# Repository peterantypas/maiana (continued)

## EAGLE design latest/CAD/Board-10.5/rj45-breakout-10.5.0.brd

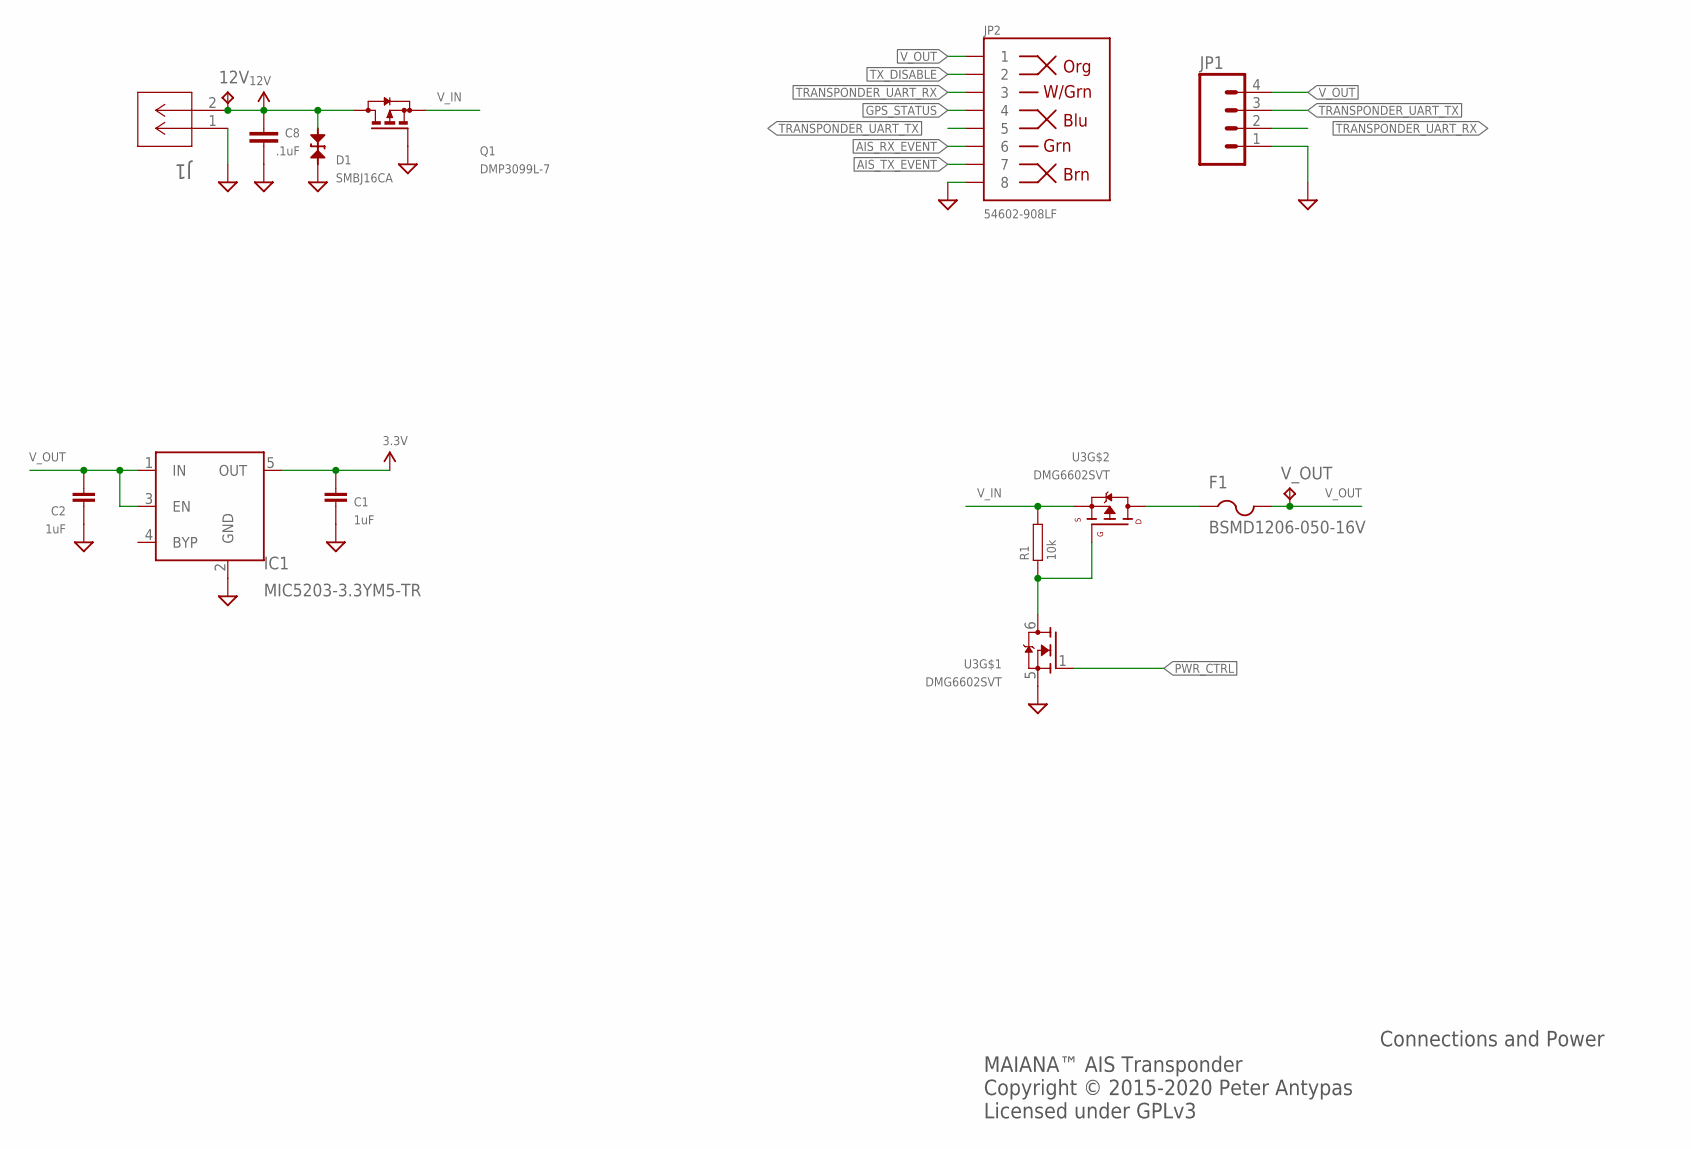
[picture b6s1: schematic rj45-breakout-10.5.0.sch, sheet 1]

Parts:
12V: TPTP20R; TP20R
C1, C2: 1uF; 0603
C8: .1uF; 0603-CAP; PARTNO GRM188R71E223KA01D
D1: SMBJ16CA; SMB-BIDIR
F1: BSMD1206-050-16V; R1206
IC1: MIC5203-3.3YM5-TR; SOT23-5
J1: OSTVN02A150; CONN_OSTVN02A150_OST
JP1: M04PTH; 1X04
JP2: 54602-908LF; RJ45-8
Q1: DMP3099L-7; SOT23
R1: 10k; 0603
U3: DMG6602SVT; SOT23-6
V_OUT: TPTP20R; TP20R

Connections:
3.3V: C1.P$1 (1), IC1.5 (OUT); also elsewhere on the board
12V: 12V.TP, C8.1, D1.A, J1.2, Q1.3 (D)
AIS_RX_EVENT: JP2.6; also elsewhere on the board
AIS_TX_EVENT: JP2.7; also elsewhere on the board
GND: C1.P$2 (2), C2.P$2 (2), C8.2, D1.C, IC1.2 (GND), J1.1, JP1.1, JP2.8, Q1.1 (G), U3.5 (S); also elsewhere on the board
GPS_STATUS: JP2.4; also elsewhere on the board
unnamed: R1.P$1, U3.3 (G), U3.6 (D)
unnamed: F1.1, U3.4 (D)
PWR_CTRL: U3.1 (G); also elsewhere on the board
TRANSPONDER_UART_RX: JP1.2, JP2.3
TRANSPONDER_UART_TX: JP1.3, JP2.5
TX_DISABLE: JP2.2; also elsewhere on the board
V_IN: Q1.2 (S), R1.P$2, U3.2 (S); also elsewhere on the board
V_OUT: C2.P$1 (1), F1.2, IC1.1 (IN), IC1.3 (EN), JP1.4, JP2.1, V_OUT.TP

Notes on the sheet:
MAIANA™ AIS Transponder Copyright © 2015-2020 Peter Antypas Licensed under GPLv3
Connections and Power

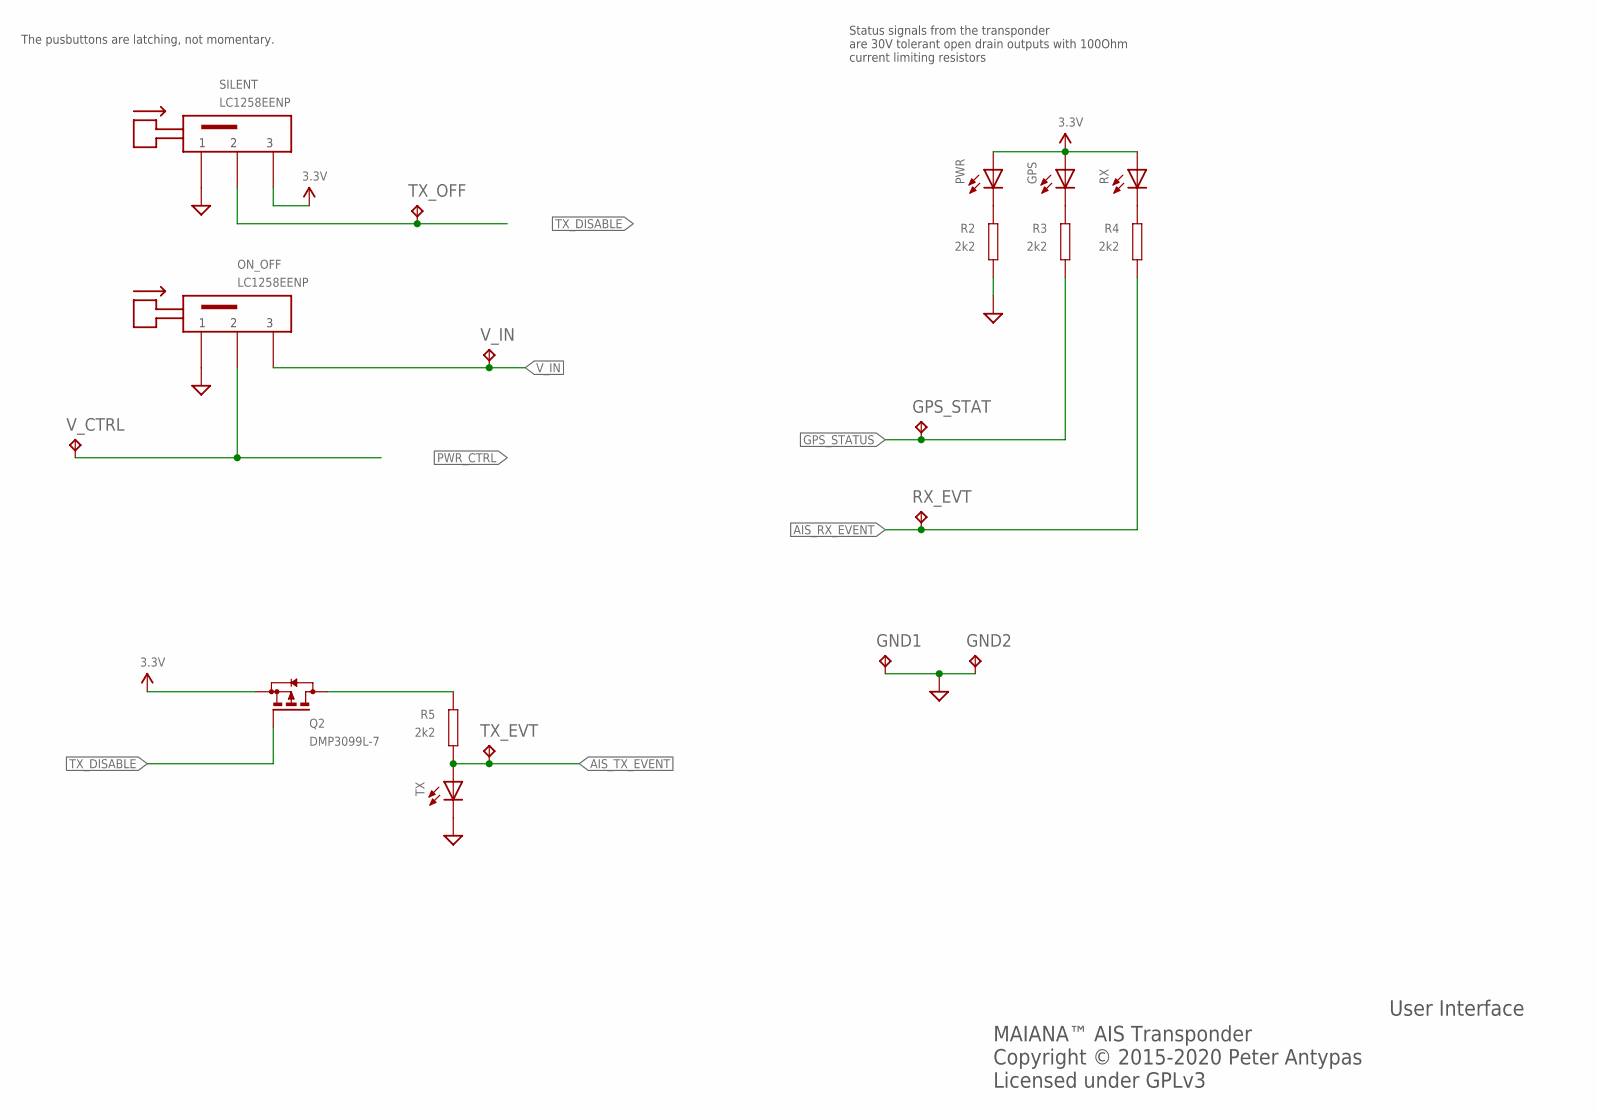
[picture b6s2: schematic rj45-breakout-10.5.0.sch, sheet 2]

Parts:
GND1, GND2: TPTP20R; TP20R
GPS: LEDCHIPLED_1206; CHIPLED_1206
GPS_STAT: TPTP20R; TP20R
ON_OFF: LC1258EENP; LC1258XXNP
PWR: LEDCHIPLED_1206; CHIPLED_1206
Q2: DMP3099L-7; SOT23
R2, R3, R4, R5: 2k2; 0603
RX: LEDCHIPLED_1206; CHIPLED_1206
RX_EVT: TPTP20R; TP20R
SILENT: LC1258EENP; LC1258XXNP
TX: LEDCHIPLED_1206; CHIPLED_1206
TX_EVT: TPTP20R; TP20R
TX_OFF: TPTP20R; TP20R
V_CTRL: TPTP20R; TP20R
V_IN: TPTP20R; TP20R

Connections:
3.3V: GPS.A, PWR.A, Q2.2 (S), RX.A, SILENT.P$3 (3); also elsewhere on the board
AIS_RX_EVENT: R4.P$2, RX_EVT.TP; also elsewhere on the board
AIS_TX_EVENT: R5.P$2, TX.A, TX_EVT.TP; also elsewhere on the board
GND: GND1.TP, GND2.TP, ON_OFF.P$1 (1), R2.P$2, SILENT.P$1 (1), TX.C; also elsewhere on the board
GPS_STATUS: GPS_STAT.TP, R3.P$2; also elsewhere on the board
unnamed: PWR.C, R2.P$1
unnamed: GPS.C, R3.P$1
unnamed: R4.P$1, RX.C
unnamed: Q2.3 (D), R5.P$1
PWR_CTRL: ON_OFF.P$2 (2), V_CTRL.TP; also elsewhere on the board
TX_DISABLE: Q2.1 (G), SILENT.P$2 (2), TX_OFF.TP; also elsewhere on the board
V_IN: ON_OFF.P$3 (3), V_IN.TP; also elsewhere on the board

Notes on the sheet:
MAIANA™ AIS Transponder Copyright © 2015-2020 Peter Antypas Licensed under GPLv3
User Interface
The pusbuttons are latching, not momentary.
Status signals from the transponder are 30V tolerant open drain outputs with 100Ohm current limiting resistors

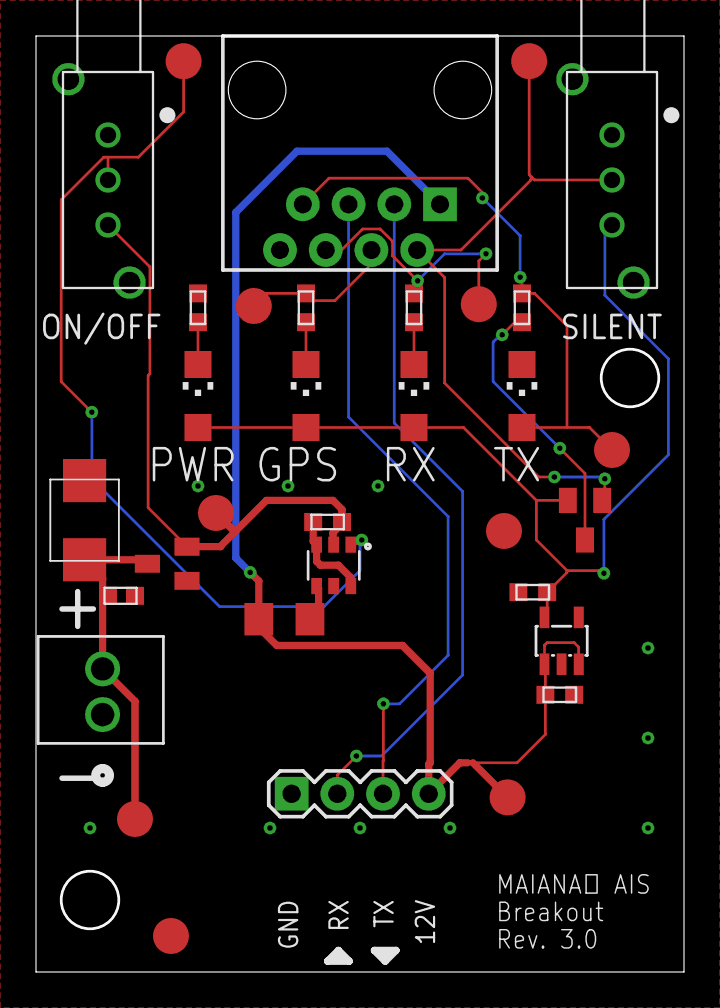
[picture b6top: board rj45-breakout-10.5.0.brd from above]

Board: 2 copper layers, 36.0 x 52.0 mm, 33 parts (0 on the bottom side), 18 nets.
